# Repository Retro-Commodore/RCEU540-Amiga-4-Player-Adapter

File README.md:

# RCEU540-Amiga-4-Player-Adapter
An adapter that plugs into the Amiga's parallel port to grant 3rd and 4th joystick port.  
  
## BOM
2x db9 male (for wires)  
1x db25 male (for wires)  
  
### Optional  
2x 1x2 2.54mm/0.1" SIL header  
2x jumpers  
  
The optional part is to enable 5v supply to the joystick (i.e. autofire etc)  

## Casing
An adapter case is available on [Thingiverse](https://www.thingiverse.com/thing:4112671)  

## Notes
The adapter is quite stable plugged into the amiga and 2 joysticks connected to it.

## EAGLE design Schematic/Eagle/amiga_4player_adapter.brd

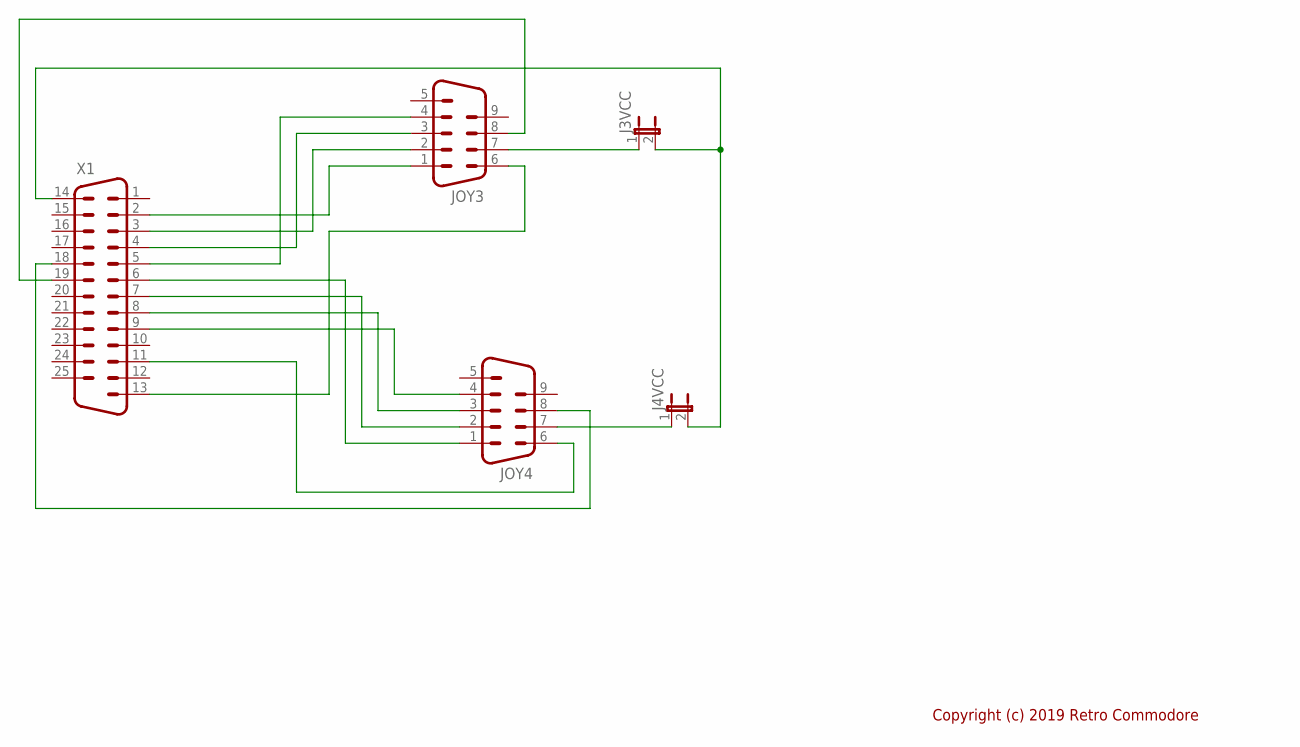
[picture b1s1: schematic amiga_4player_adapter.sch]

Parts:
J3VCC, J4VCC: JP1E; JP1
JOY3, JOY4: M09D
X1: M25D

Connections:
GND: JOY3.8, JOY4.8, X1.18, X1.19
J3_DOWN: JOY3.2, X1.3
J3_FIRE: JOY3.6, X1.13
J3_LEFT: JOY3.3, X1.4
J3_RIGHT: JOY3.4, X1.5
J3_UP: JOY3.1, X1.2
J3_VCC: J3VCC.1, JOY3.7
J4_DOWN: JOY4.2, X1.7
J4_FIRE: JOY4.6, X1.11
J4_LEFT: JOY4.3, X1.8
J4_RIGHT: JOY4.4, X1.9
J4_UP: JOY4.1, X1.6
J4_VCC: J4VCC.1, JOY4.7
VCC: J3VCC.2, J4VCC.2, X1.14

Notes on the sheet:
Copyright (c) 2019 Retro Commodore

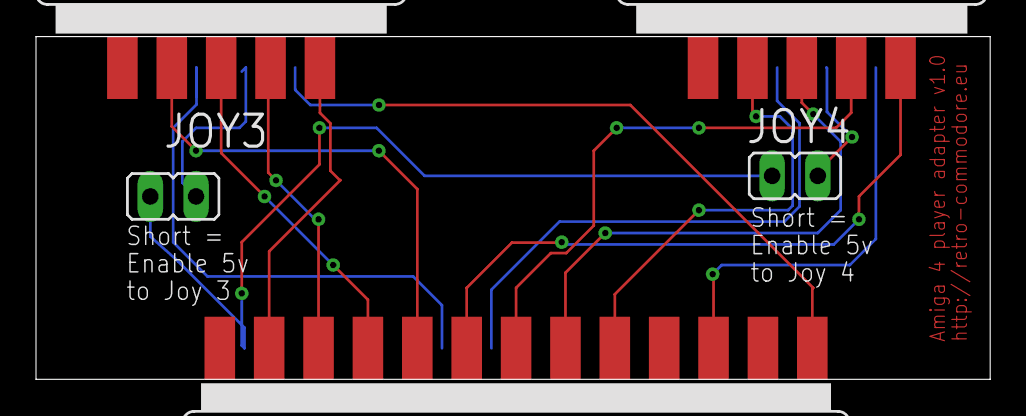
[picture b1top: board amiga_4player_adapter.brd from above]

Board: 2 copper layers, 53.0 x 19.0 mm, 5 parts (0 on the bottom side), 14 nets.

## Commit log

2020-10-14 Added pics + schematics
